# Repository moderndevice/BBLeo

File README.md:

Bare Bones Leonardo, a breadboardable Arduino Leonardo clone
==========

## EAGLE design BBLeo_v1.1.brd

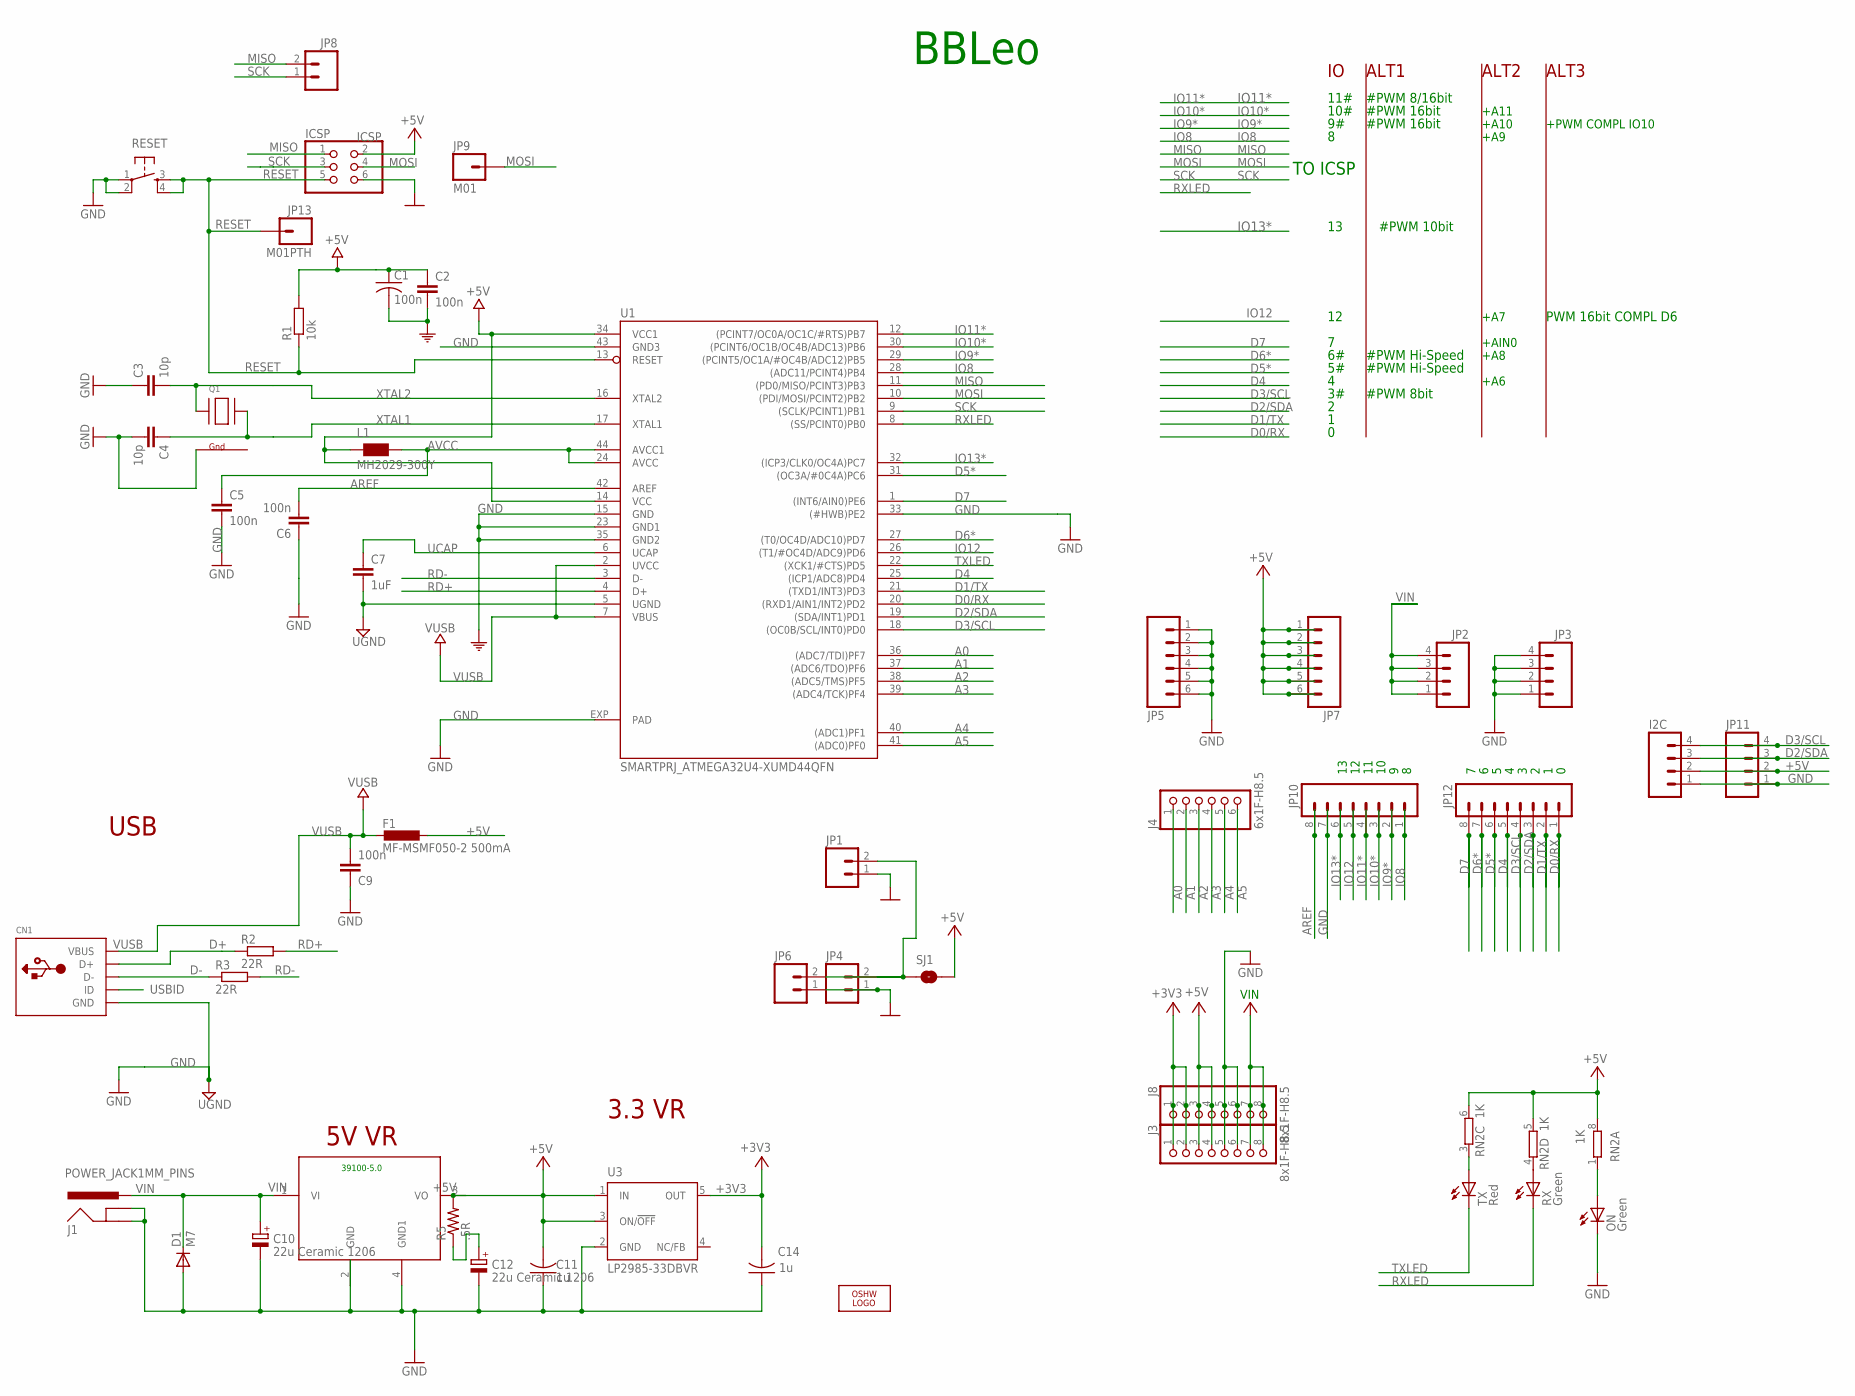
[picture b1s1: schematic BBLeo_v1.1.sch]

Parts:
C1: 100n; C0603K
C2, C5, C6, C9: 100n; C0603-ROUND
C3, C4: 10p; C0603-ROUND
C7: 1uF; C0603-ROUND
C10, C12: 22u Ceramic 1206; SMC_B
C11, C14: 1u; C0603K
CN1: USBMINIB; USB-MINIB
D1: M7; SMB
F1: MF-MSMF050-2 500mA; L1812
I2C: M04SQ_SILK; 1X04_SQ_SILK
IC1: MIC39100DB; SOT223WTAB
ICSP: ICSP; 2X03
J1: POWER_JACK1MM_PINS; POWER_JACK_1MMPTH.PAC
J3, J8: 8x1F-H8.5; 1X08
J4: 6x1F-H8.5; 1X06
JP1, JP4, JP6, JP8: M02PTH; 1X02
JP2, JP3, JP11: M04SQ_SILK; 1X04_SQ_SILK
JP5, JP7: M06SQ_SILK; 1X06_SQ_SILK
JP9: M01; 1X01
JP10, JP12: M08; 1X08
JP13: M01PTH; 1X01
L1: MH2029-300Y; 0805
LOGO1: OSHW_LOGO_FILLX0100-NT; OSHW_FILLX100_NOTEXT
ON: Green; CHIPLED_0805
Q1: XTAL-4-3225; NX3225
R1: 10k; R0603
R2, R3: 22R; R0603
R5: .5R; R0603
RESET: 6MM_SWITCH6MM_SWITCH; 6MM_SWITCH
RN2: 1K; CAY16
RX: Green; CHIPLED_0805
SJ1: SOLDERJUMPERNC2; SJ_2S-NOTRACE
TX: Red; CHIPLED_0805
U1: SMARTPRJ_ATMEGA32U4-XUMD44QFN; MD__QFN44ML7X7
U3: LP2985-33DBVR; SOT23-DBV

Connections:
+3V3: C14.2, J3.1, J3.2, J8.1, J8.2, U3.5 (OUT)
+5V: C1.1, C2.1, C11.2, F1.1, I2C.2, IC1.3 (VO), ICSP.2, J3.3, J3.4, J8.3, J8.4, JP7.1, JP7.2, JP7.3, JP7.4, JP7.5, JP7.6, JP11.2, L1.1, R1.2, R5.2, RN2.5 (2), RN2.6 (2), RN2.8 (2), SJ1.2, U1.14 (VCC), U1.34 (VCC1), U3.1 (IN), U3.3 (ON/!OFF)
A0: J4.1, U1.36 ((ADC7/TDI)PF7)
A1: J4.2, U1.37 ((ADC6/TDO)PF6)
A2: J4.3, U1.38 ((ADC5/TMS)PF5)
A3: J4.4, U1.39 ((ADC4/TCK)PF4)
A4: J4.5, U1.40 ((ADC1)PF1)
A5: J4.6, U1.41 ((ADC0)PF0)
AREF: C6.2, JP10.8, U1.42 (AREF)
AVCC: C5.1, L1.2, U1.24 (AVCC), U1.44 (AVCC1)
D0/RX: JP12.1, U1.20 ((RXD1/AIN1/INT2)PD2)
D1/TX: JP12.2, U1.21 ((TXD1/INT3)PD3)
D2/SDA: I2C.3, JP11.3, JP12.3, U1.19 ((SDA/INT1)PD1)
D3/SCL: I2C.4, JP11.4, JP12.4, U1.18 ((OC0B/SCL/INT0)PD0)
D4: JP12.5, U1.25 ((ICP1/ADC8)PD4)
D5*: JP12.6, U1.31 ((OC3A/#0C4A)PC6)
D6*: JP12.7, U1.27 ((T0/OC4D/ADC10)PD7)
D7: JP12.8, U1.1 ((INT6/AIN0)PE6)
D+: CN1.D+, R2.1
D-: CN1.D-, R3.1
G2: Q1.2 (G2)
GND: C1.2, C2.2, C3.1, C4.2, C5.2, C6.1, C9.1, C10.-, C11.1, C12.-, C14.1, CN1.GND, D1.A, I2C.1, IC1.2 (GND), IC1.4 (GND1), ICSP.6, J1.GND, J1.GNDBREAK, J3.5, J3.6, J8.5, J8.6, JP1.1, JP3.1, JP3.2, JP3.3, JP3.4, JP4.1, JP5.1, JP5.2, JP5.3, JP5.4, JP5.5, JP5.6, JP6.1, JP10.7, JP11.1, ON.C, Q1.4 (G1), RESET.1, RESET.2 (P1), U1.15 (GND), U1.23 (GND1), U1.33 ((#HWB)PE2), U1.35 (GND2), U1.43 (GND3), U1.EXP (PAD), U3.2 (GND)
GND1: C7.2, U1.5 (UGND)
IO8: JP10.1, U1.28 ((ADC11/PCINT4)PB4)
IO9*: JP10.2, U1.29 ((PCINT5/OC1A/#OC4B/ADC12)PB5)
IO10*: JP10.3, U1.30 ((PCINT6/OC1B/OC4B/ADC13)PB6)
IO11*: JP10.4, U1.12 ((PCINT7/OC0A/OC1C/#RTS)PB7)
IO12: JP10.5, U1.26 ((T1/#OC4D/ADC9)PD6)
IO13*: JP10.6, U1.32 ((ICP3/CLK0/OC4A)PC7)
MISO: ICSP.1, JP8.2, U1.11 ((PD0/MISO/PCINT3)PB3)
MOSI: ICSP.4, JP9.1, U1.10 ((PDI/MOSI/PCINT2)PB2)
unnamed: RN2.3 (1), TX.A
unnamed: ON.A, RN2.1
unnamed: C12.+, R5.1
unnamed: RN2.4 (1), RX.A
RD+: R2.2, U1.4 (D+)
RD-: R3.2, U1.3 (D-)
RESET: ICSP.5, JP13.1, R1.1, RESET.3 (S), RESET.4 (S1), U1.13 (RESET)
RXLED: RX.C, U1.8 ((SS/PCINT0)PB0)
S5V: JP1.2, JP4.2, JP6.2, SJ1.1
SCK: ICSP.3, JP8.1, U1.9 ((SCLK/PCINT1)PB1)
TXLED: TX.C, U1.22 ((XCK1/#CTS)PD5)
UCAP: C7.1, U1.6 (UCAP)
USBID: CN1.ID
VIN: C10.+, D1.C, IC1.1 (VI), J1.PWR, J3.7, J3.8, J8.7, J8.8, JP2.1, JP2.2, JP2.3, JP2.4
VUSB: C9.2, CN1.VBUS, F1.2, U1.2 (UVCC), U1.7 (VBUS)
XTAL1: C4.1, Q1.3 (X2), U1.17 (XTAL1)
XTAL2: C3.2, Q1.1 (X1), U1.16 (XTAL2)

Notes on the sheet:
BBLeo
USB
TO ICSP
10#
11#
#PWM 8bit
#PWM Hi-Speed
#PWM 8/16bit
#PWM 16bit
PWM 16bit COMPL D6
#PWM 10bit
+A6
+A7
+A11
+A10
+A8
+A9
+PWM COMPL IO10
+AIN0
ALT1
ALT2
ALT3
5V VR
3.3 VR
VIN
39100-5.0

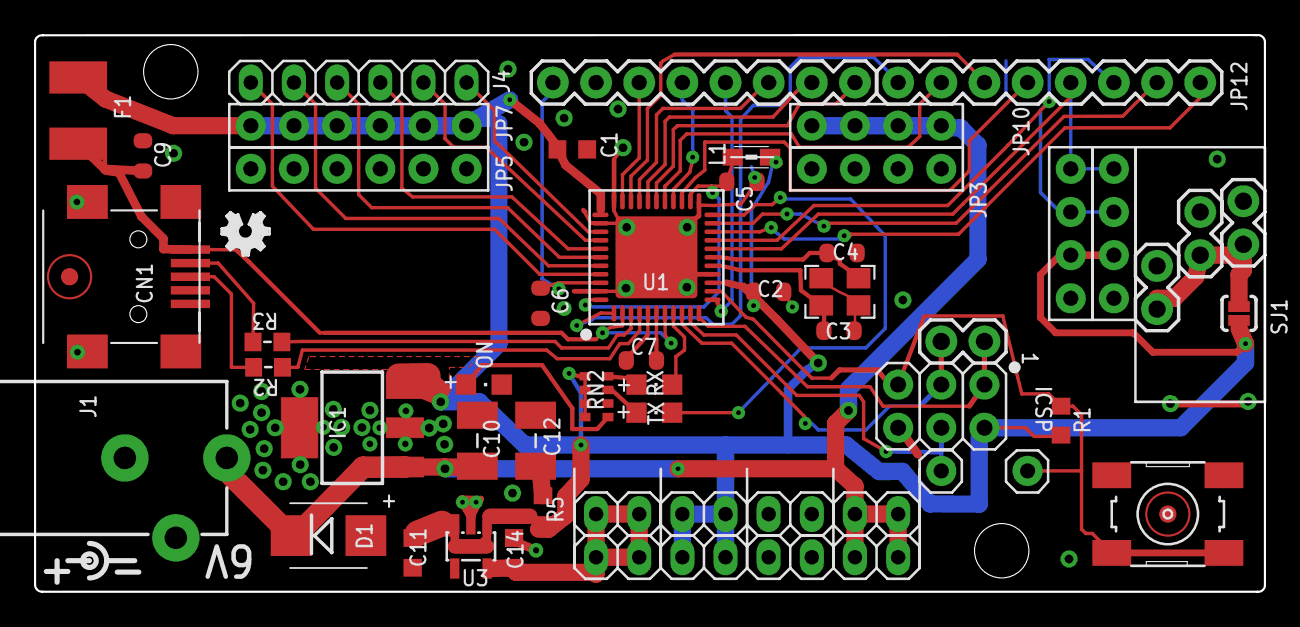
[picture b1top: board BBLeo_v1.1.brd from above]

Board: 2 copper layers, 72.4 x 32.8 mm, 52 parts (0 on the bottom side), 46 nets.

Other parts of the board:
RST: FIDUCIAL
U$2: FIDUCIAL

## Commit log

2014-12-02 Added actual board design files
2017-10-03 Create new file
